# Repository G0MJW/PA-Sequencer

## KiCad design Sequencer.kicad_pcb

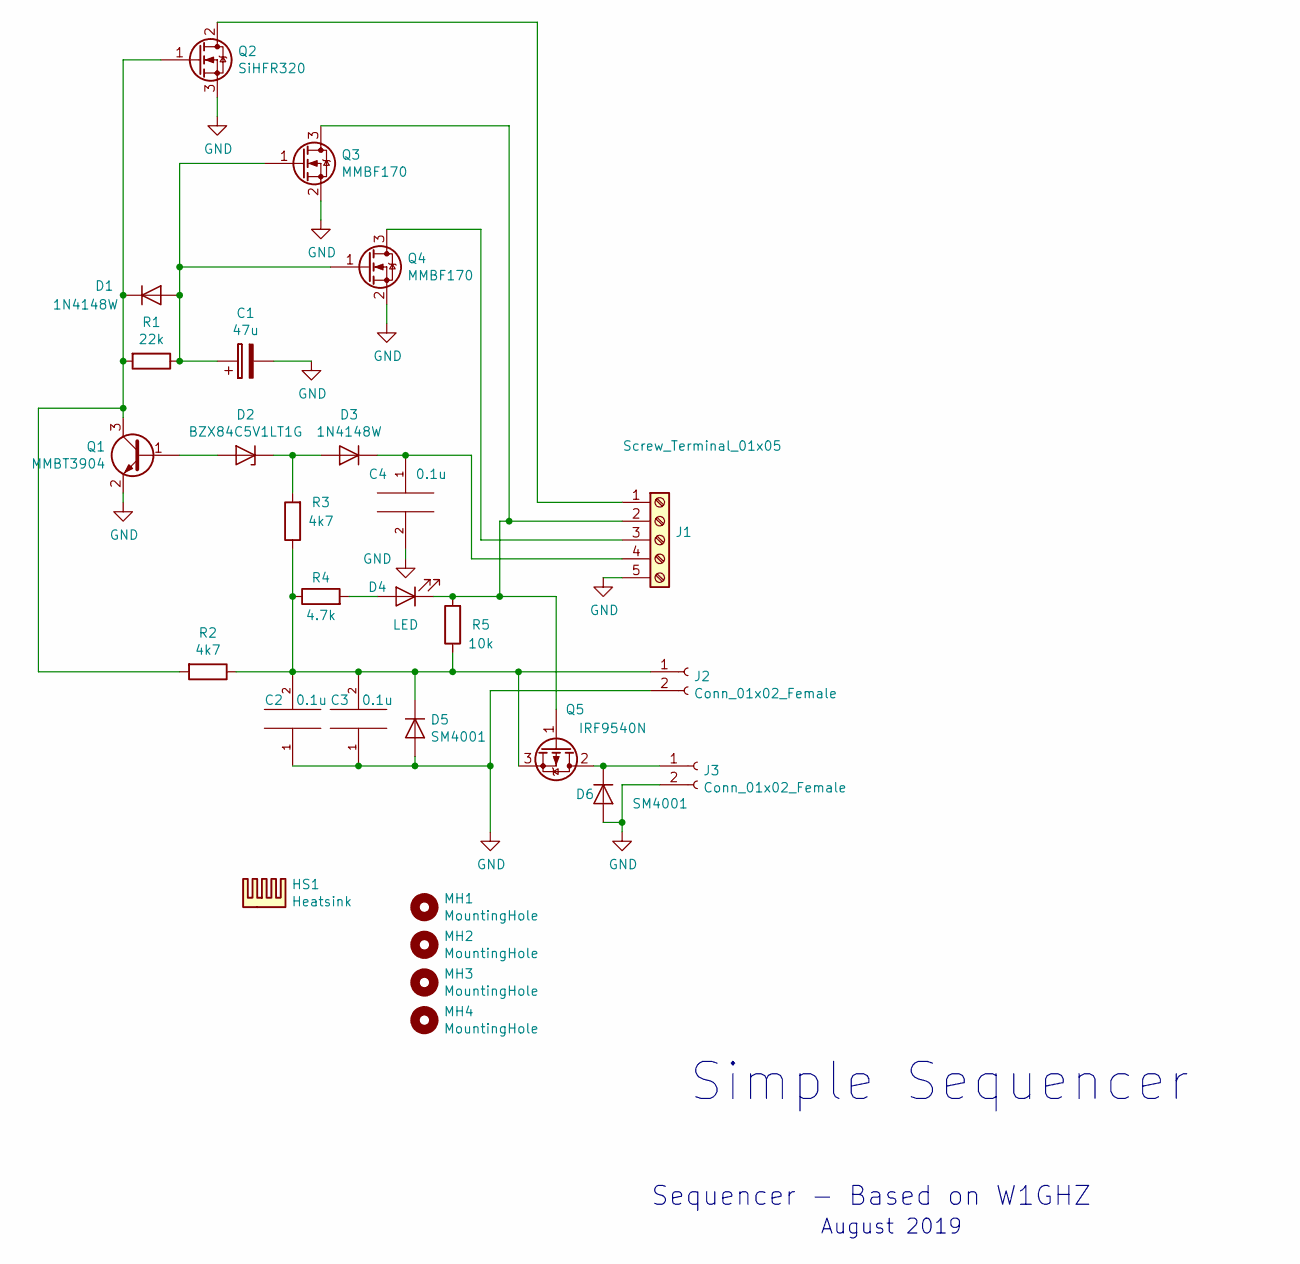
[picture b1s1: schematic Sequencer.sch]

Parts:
C1: 47u; CP_Elec_6.3x5.4
C2, C3, C4: 0.1u; C_0805_2012Metric
D1, D3: 1N4148W; D_SOD-123
D2: BZX84C5V1LT1G; D_SOT-23_ANK
D4: LED; LED_0805_2012Metric_Castellated
D5, D6: SM4001; D_MELF
HS1: Heatsink; Heatsink_Fischer_SK104-STC-STIC_35x13mm_2xDrill2.5mm
J1: Screw_Terminal_01x05; TerminalBlock_bornier-5_P5.08mm
J2, J3: Conn_01x02_Female; Anderson_Powerpole-staple-Nx2
MH1, MH2, MH3, MH4: MountingHole; MountingHole_3.2mm_M3
Q1: MMBT3904; SOT-23
Q2: SiHFR320; TO-252-3_TabPin2
Q3, Q4: MMBF170; SOT-23
Q5: IRF9540N; TO-220-3_Vertical
R1: 22k; R_0805_2012Metric
R2, R3: 4k7; R_0805_2012Metric
R4: 4.7k; R_0805_2012Metric
R5: 10k; R_0805_2012Metric

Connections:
GND: C1.2, C2.1, C3.1, C4.2, D5.2 (A), D6.2 (A), J1.5, J2.2, J3.2, Q1.2 (E), Q2.3 (S), Q3.2 (S), Q4.2 (S)
unnamed: C1.1, D1.2 (A), Q3.1 (G), Q4.1 (G), R1.1
unnamed: C2.2, C3.2, D5.1 (K), J2.1, Q5.3 (S), R2.1, R3.1, R4.1, R5.1
unnamed: C4.1, D3.1 (K), J1.4
unnamed: D1.1 (K), Q1.3 (C), Q2.1 (G), R1.2, R2.2
unnamed: D2.1 (K), D3.2 (A), R3.2
unnamed: D2.2 (A), Q1.1 (B)
unnamed: D4.1 (K), J1.2, Q3.3 (D), Q5.1 (G), R5.2
unnamed: D4.2 (A), R4.2
unnamed: D6.1 (K), J3.1, Q5.2 (D)
unnamed: J1.1, Q2.2 (D)
unnamed: J1.3, Q4.3 (D)

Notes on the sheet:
Simple Sequencer
August 2019
Sequencer - Based on W1GHZ

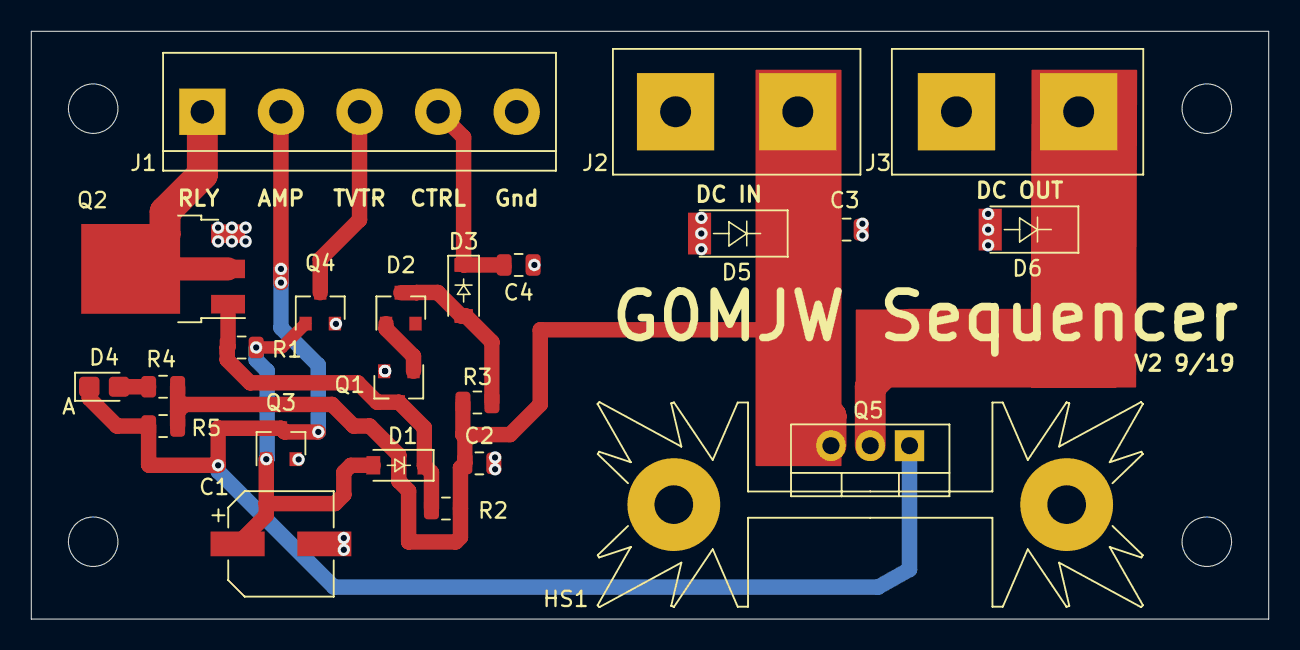
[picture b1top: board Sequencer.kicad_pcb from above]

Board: 2 copper layers, 80.0 x 38.0 mm, 28 parts (0 on the bottom side), 12 nets.

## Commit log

2019-08-20 First Commmit
2019-09-24 Heatsink traces
    Update
